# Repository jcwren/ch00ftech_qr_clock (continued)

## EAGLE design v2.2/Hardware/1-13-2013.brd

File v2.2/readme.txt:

_      ___   ___   __ _            _     
      | |    / _ \ / _ \ / _| |          | |    
   ___| |__ | | | | | | | |_| |_ ___  ___| |__  
  / __| '_ \| | | | | | |  _| __/ _ \/ __| '_ \ 
 | (__| | | | |_| | |_| | | | ||  __/ (__| | | |
  \___|_| |_|\___/ \___/|_|  \__\___|\___|_| |_|
                                                
QR Clock Readme v2.1 4/2/2012

By: Michael Ciuffo
ch00f@ch00ftech.com

http://ch00ftech.com/qrclock

*********************
*Package Description*
*********************

This package contains the following two folders:

--Hardware
Eagle files for schematic and PCB layout of the device along with a PNG schematic.  Digikey part numbers are included in part attributes. The symbol for D7 is backwards in the schematic.  Photodiodes should be reverse biased.

--Firmware
Firmware and Makefile for the QR clock.  Should compile with with avrdude version 5.11.1.

**********
*Versions*
**********

2.2 - Fixed a bug resulting from a misinterpretation of the QR code generation process.  After the XOR step, only the *first* zero is supposed to be removed even if more than one is there.  Modified code to only remove first zero.  This bug caused an invalid QR code with very specific inputs such as “00Y9PT0040016002”

**********
*Warnings*
**********

THIS IS NOT A TUTORIAL! These are the design files that I used to create what you see on my blog.  They are meant to be used as reference only.  If you do not understand how the project is supposed to work, do not begin working on it.  Given how haphazardly a lot of my projects are put together, in all likelihood, the designs presented herein won't actually work due to changes I made post publication.

I am a EE, not a coder.  My programming practices are questionable at best.  If you learn anything from working on this project, please don't let it be how to code like I do.

*********
*License*
*********

The contents of this package are released to you under the Creative Commons Attribution-NonCommercial 3.0 Unported license.

This means that you are free to distribute this package and edit it as you see fit.  All works based on this package must provide attribution in some form to me.  A simple link to the blog post along with a description of what you used will suffice.

You may not use this package for any commercial ventures without my consent (but I'm usually cool with it, you just have to send me an email and ask nicely).

More information here:

http://creativecommons.org/licenses/by-nc/3.0/deed.en_US

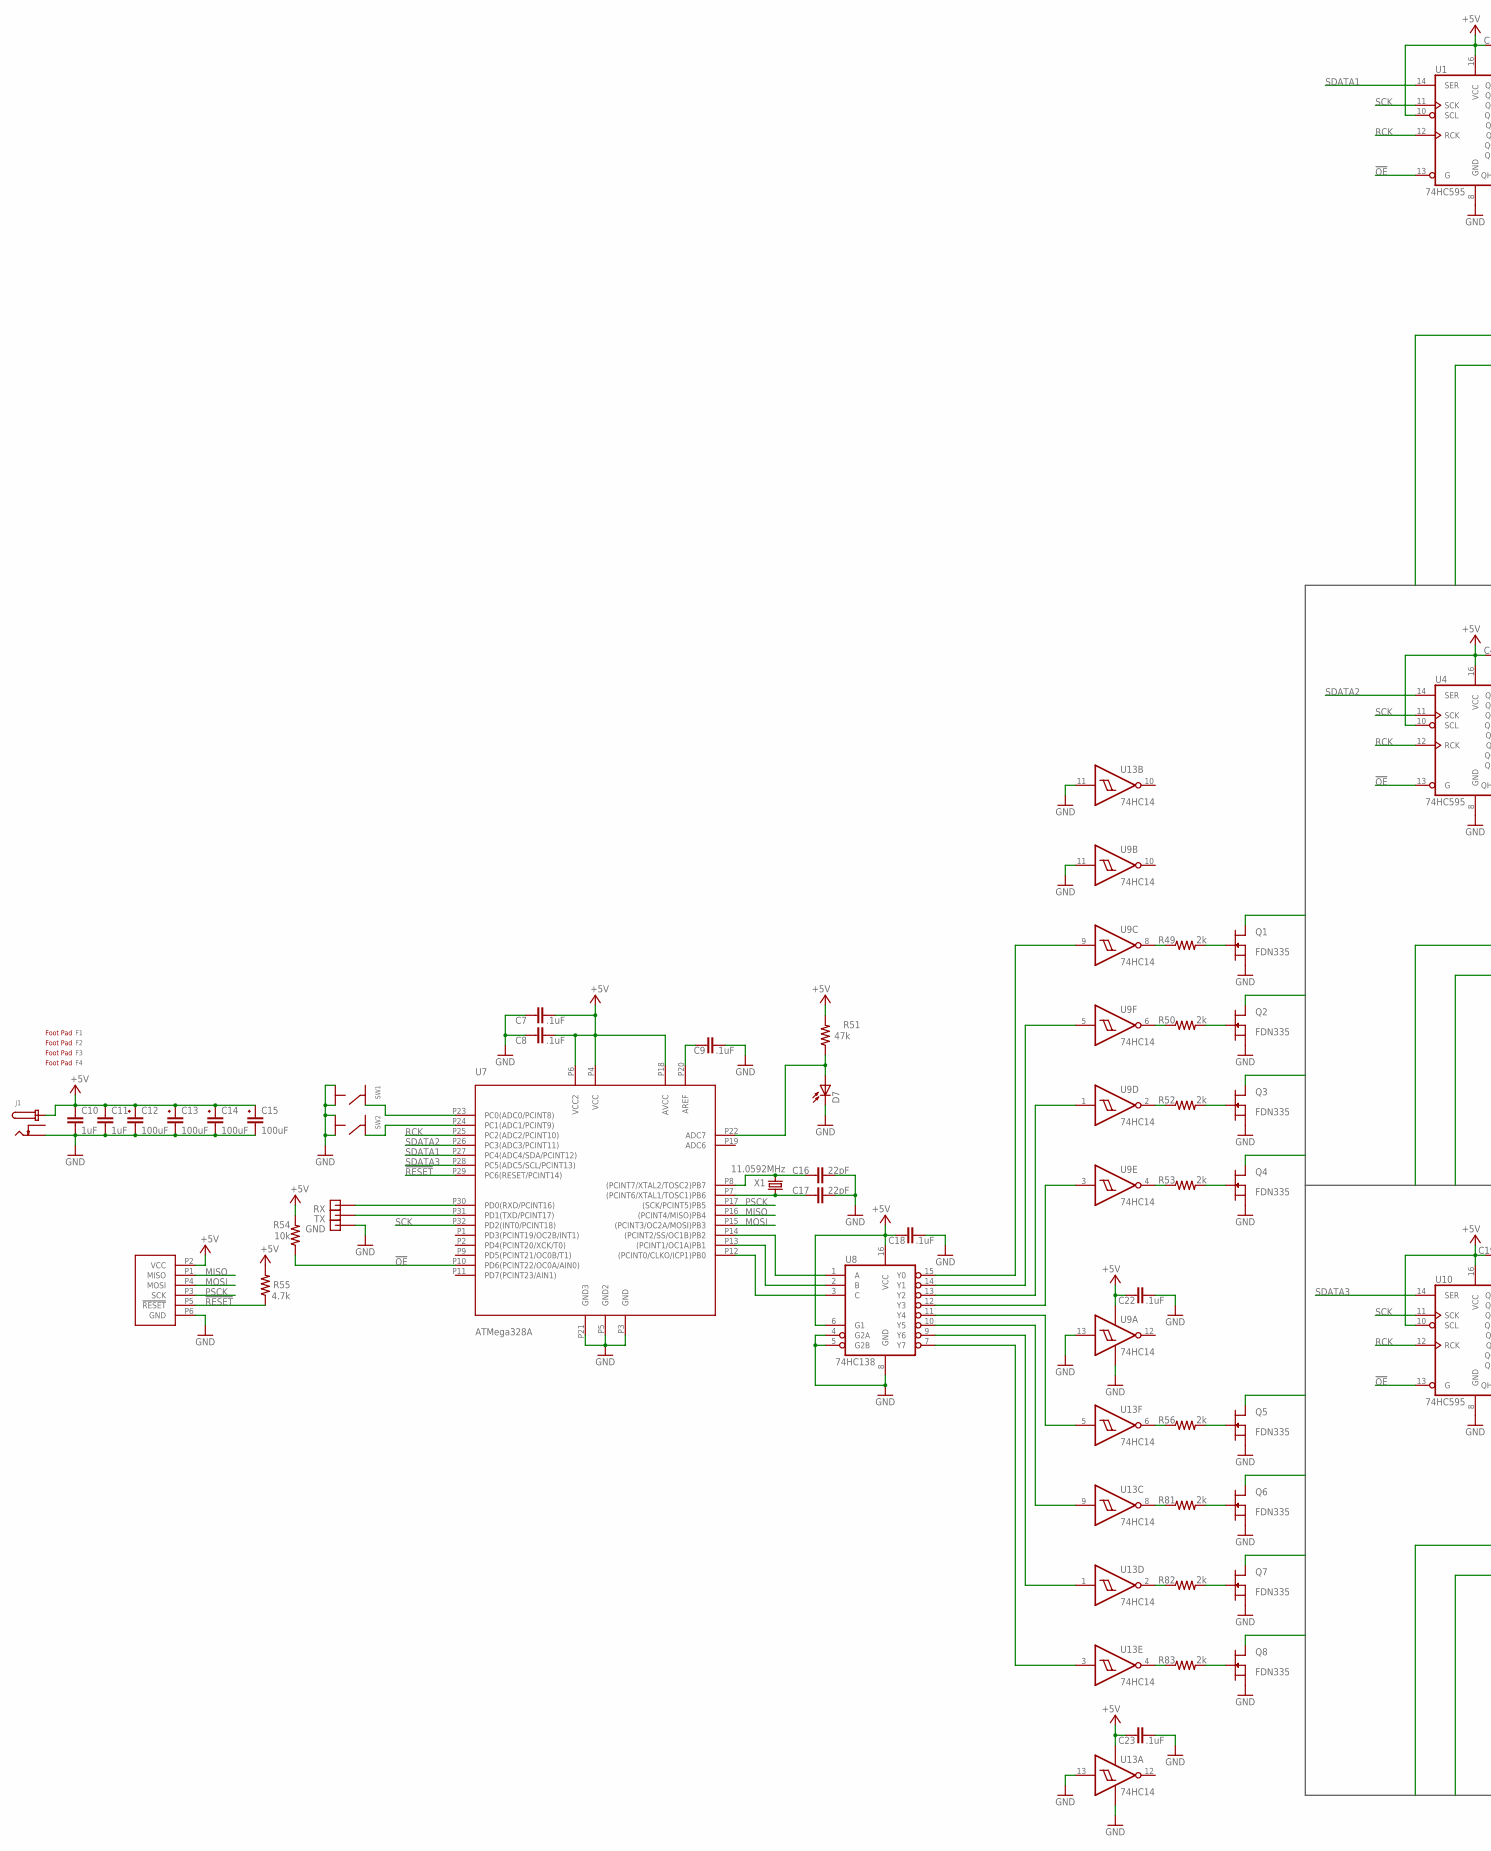
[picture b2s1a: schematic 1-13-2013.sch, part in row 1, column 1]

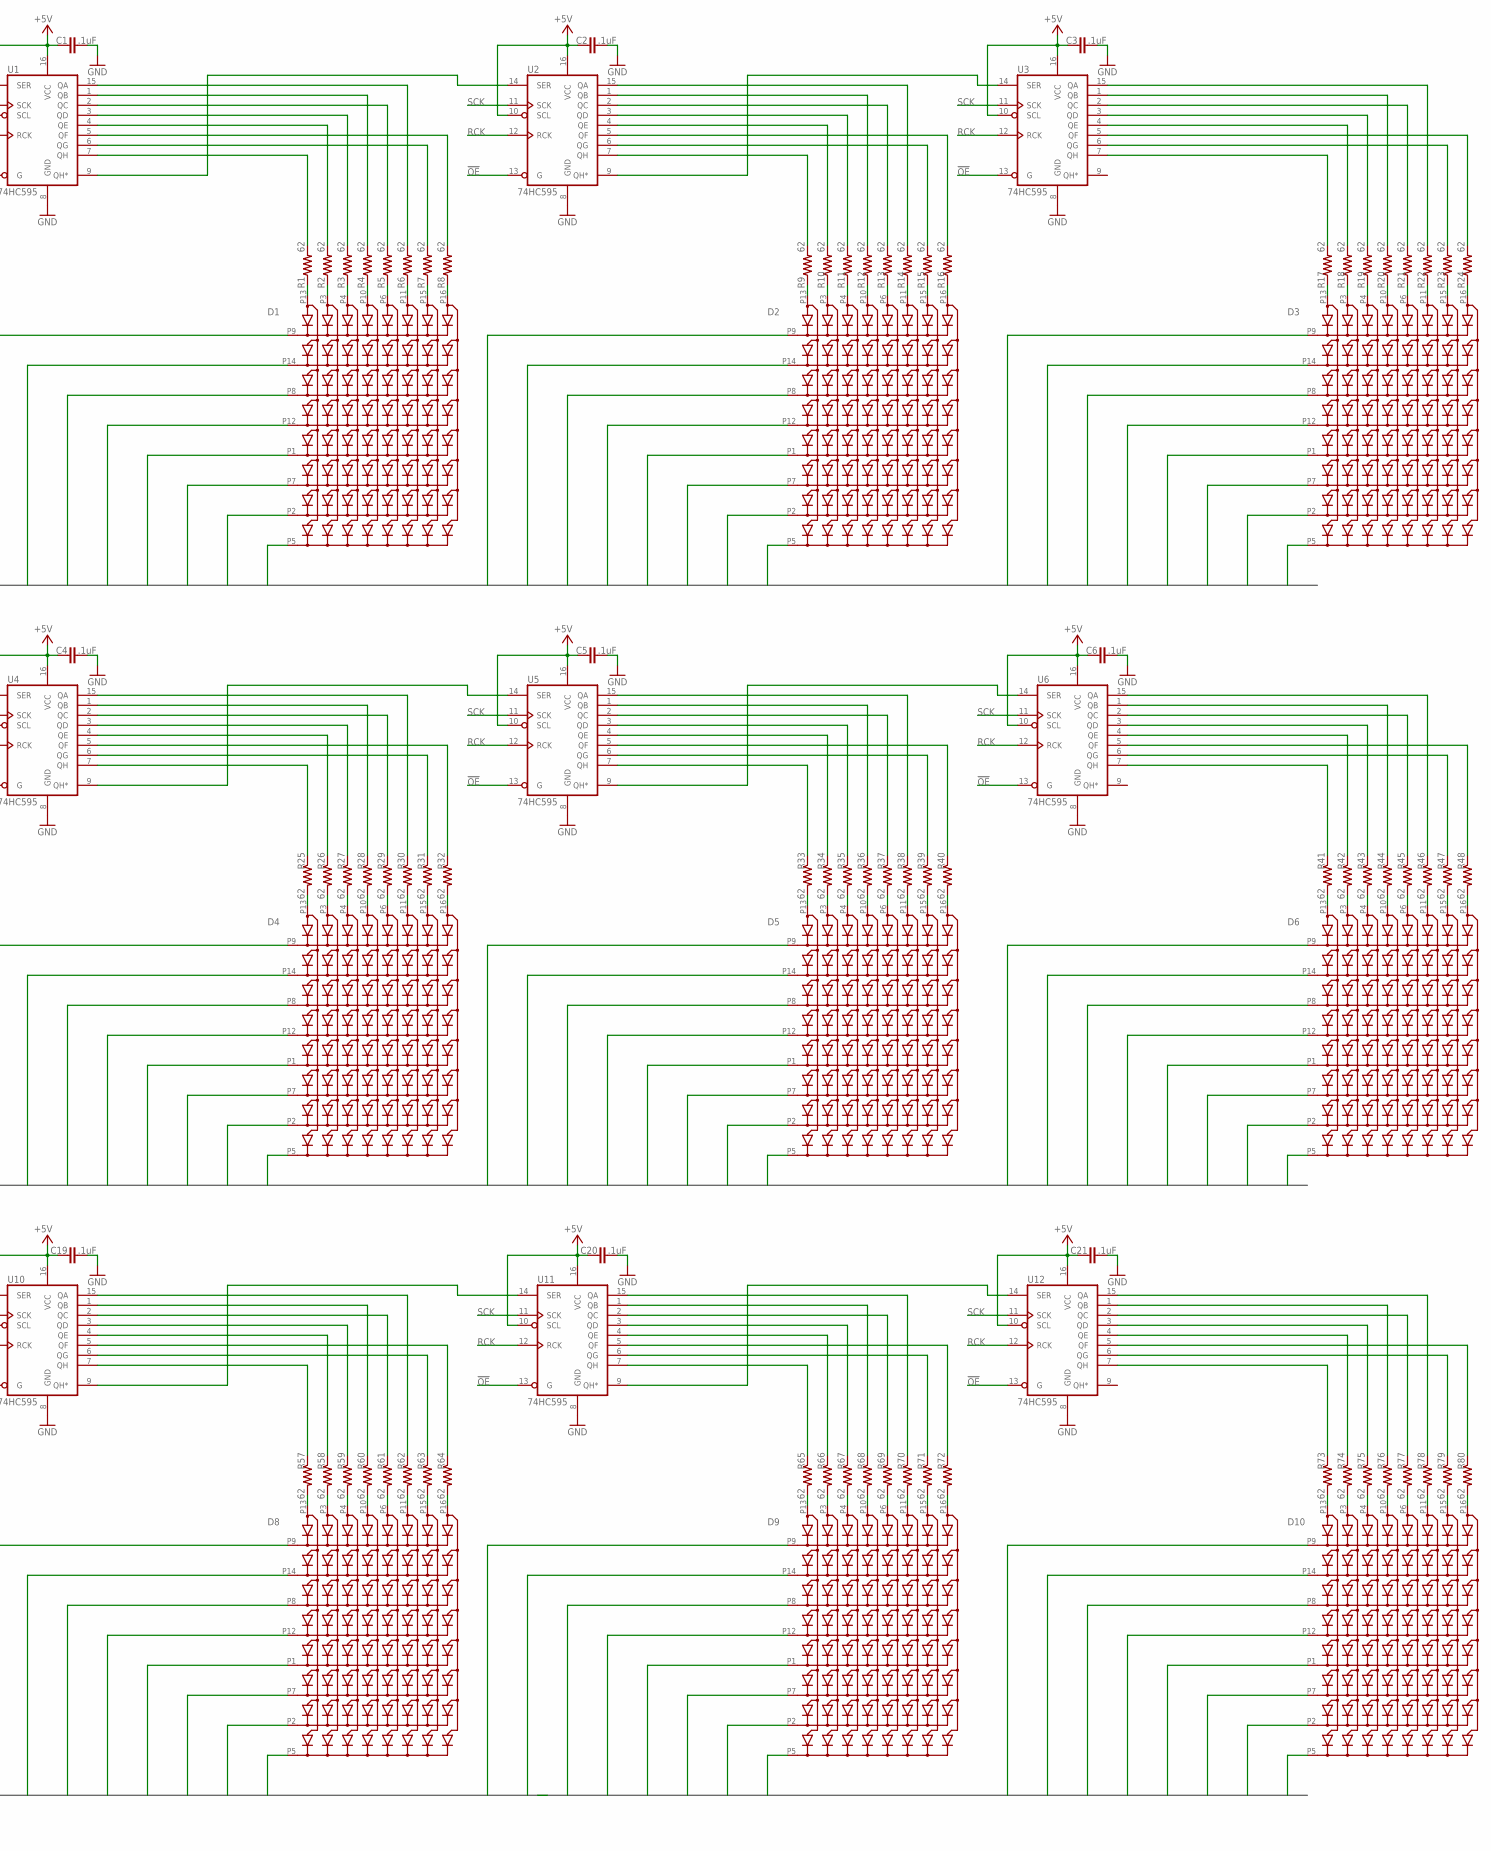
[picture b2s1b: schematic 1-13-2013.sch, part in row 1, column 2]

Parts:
C1, C2, C3, C4, C5, C6, C7, C8, C9, C18, C19, C20, C21, C22, C23: .1uF; 0603/1608METRIC
C10, C11: 1uF; 0603/1608METRIC
C12, C13: 100uF; CAP-UWX-6.3
C14, C15: 100uF; CAP-UWX-6.3; MANPARTNO UWX1C101MCL1GB
C16, C17: 22pF; 0603/1608METRIC; VOLTAGE 25V
D1, D2, D3, D4, D5, D6, D8, D9, D10: WHITE; HS-2085BX
D7: TEPT4400; LED3MM
F1, F2, F3, F4: RUBBER-FOOT; SJ-5518
GND: HEADERPIN
J1: DC-BARREL-JACK-SWITCH; PJ-075DH-SMT-TR
J2: PROGHEADER-PINS; ATMEL-PROGRAMMING-HEADER
Q1, Q2, Q3, Q4, Q5, Q6, Q7, Q8: FDN335; SOT23
R1: 62; 0603/1608METRIC
R2, R3, R4, R5, R6, R7, R8, R9, R10, R11, R12, R13, R14, R15, R16, R17, R18, R19, R20, R21, R22, R23, R24, R25, R26, R27, R28, R29, R30, R31, R32, R33, R34, R35, R36, R37, R38, R39, R40, R41, R42, R43, R44, R45, R46, R47, R48, R57, R58, R59, R60, R61, R62, R63, R64, R65, R66, R67, R68, R69, R70, R71, R72, R73, R74, R75, R76, R77, R78, R79, R80: 62; 0603/1608METRIC; TOLERANCE 5%; MANPARTNO RC0603JR-0762RL
R49, R50, R52, R53, R56, R81, R82, R83: 2k; 0603/1608METRIC
R51: 47k; 0603/1608METRIC
R54: 10k; 0603/1608METRIC
R55: 4.7k; 0603/1608METRIC
RX: HEADERPIN
SW1, SW2: 4mm; PTS645SM43SMTRLFS; MANPARTNO PTS645SM43SMTR LFS
TX: HEADERPIN
U1, U2, U3, U4, U5, U6, U10, U11, U12: 74HC595; SO16
U7: ATMega328A; TQFP-32
U8: 74HC138; SO16
U9, U13: 74HC14; SO14
X1: 11.0592MHz; HC49UP; MANPARTNO 9C-11.0592MEEJ-T

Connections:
!OE: R54.P1 (1), U1.13 (G), U2.13 (G), U3.13 (G), U4.13 (G), U5.13 (G), U6.13 (G), U7.P10 (PD6(PCINT22/OC0A/AIN0)), U10.13 (G), U11.13 (G), U12.13 (G)
!RESET: J2.P5 (!RESET), R55.P1 (1), U7.P29 (PC6(RESET/PCINT14))
+5V: C1.P1 (1), C2.P1 (1), C3.P1 (1), C4.P1 (1), C5.P1 (1), C6.P1 (1), C7.P1 (1), C8.P1 (1), C10.P1 (1), C11.P1 (1), C12.+ (1), C13.+ (1), C14.+ (1), C15.+ (1), C18.P1 (1), C19.P1 (1), C20.P1 (1), C21.P1 (1), C22.P1 (1), C23.P1 (1), J1.1 (PIN), J2.P2 (VCC), R51.P2 (2), R54.P2 (2), R55.P2 (2), U1.10 (SCL), U1.16 (VCC), U2.10 (SCL), U2.16 (VCC), U3.10 (SCL), U3.16 (VCC), U4.10 (SCL), U4.16 (VCC), U5.10 (SCL), U5.16 (VCC), U6.10 (SCL), U6.16 (VCC), U7.P4 (VCC), U7.P6 (VCC2), U7.P18 (AVCC), U8.6 (G1), U8.16 (VCC), U9.14 (VCC), U10.10 (SCL), U10.16 (VCC), U11.10 (SCL), U11.16 (VCC), U12.10 (SCL), U12.16 (VCC), U13.14 (VCC)
GND: C1.P2 (2), C2.P2 (2), C3.P2 (2), C4.P2 (2), C5.P2 (2), C6.P2 (2), C7.P2 (2), C8.P2 (2), C9.P2 (2), C10.P2 (2), C11.P2 (2), C12.- (2), C13.- (2), C14.- (2), C15.- (2), C16.P2 (2), C17.P2 (2), C18.P2 (2), C19.P2 (2), C20.P2 (2), C21.P2 (2), C22.P2 (2), C23.P2 (2), D7.K (C), GND.P$1, J1.2 (BARREL), J2.P6 (GND), Q1.2 (S), Q2.2 (S), Q3.2 (S), Q4.2 (S), Q5.2 (S), Q6.2 (S), Q7.2 (S), Q8.2 (S), SW1.P3, SW1.P4, SW2.P3, SW2.P4, U1.8 (GND), U2.8 (GND), U3.8 (GND), U4.8 (GND), U5.8 (GND), U6.8 (GND), U7.P3 (GND), U7.P5 (GND2), U7.P21 (GND3), U8.4 (G2A), U8.5 (G2B), U8.8 (GND), U9.7 (GND), U9.11 (I), U9.13 (I), U10.8 (GND), U11.8 (GND), U12.8 (GND), U13.7 (GND), U13.11 (I), U13.13 (I)
MISO: J2.P1 (MISO), U7.P16 ((PCINT4/MISO)PB4)
MOSI: J2.P4 (MOSI), U7.P15 ((PCINT3/OC2A/MOSI)PB3)
unnamed: D1.P13 (C1), R1.P1 (1)
unnamed: R4.P2 (2), U1.1 (QB)
unnamed: D1.P3 (C2), R2.P1 (1)
unnamed: R5.P2 (2), U1.2 (QC)
unnamed: D1.P4 (C3), R3.P1 (1)
unnamed: R14.P2 (2), U2.15 (QA)
unnamed: D1.P10 (C4), R4.P1 (1)
unnamed: R13.P2 (2), U2.2 (QC)
unnamed: D1.P6 (C5), R5.P1 (1)
unnamed: R12.P2 (2), U2.1 (QB)
unnamed: D1.P11 (C6), R6.P1 (1)
unnamed: R11.P2 (2), U2.3 (QD)
unnamed: D1.P15 (C7), R7.P1 (1)
unnamed: R10.P2 (2), U2.4 (QE)
unnamed: D1.P16 (C8), R8.P1 (1)
unnamed: R16.P2 (2), U2.5 (QF)
unnamed: U8.15 (Y0), U9.9 (I)
unnamed: D2.P13 (C1), R9.P1 (1)
unnamed: R21.P2 (2), U3.2 (QC)
unnamed: D2.P3 (C2), R10.P1 (1)
unnamed: R20.P2 (2), U3.1 (QB)
unnamed: D2.P4 (C3), R11.P1 (1)
unnamed: R19.P2 (2), U3.3 (QD)
unnamed: D2.P10 (C4), R12.P1 (1)
unnamed: R18.P2 (2), U3.4 (QE)
unnamed: D2.P6 (C5), R13.P1 (1)
unnamed: R24.P2 (2), U3.5 (QF)
unnamed: D2.P11 (C6), R14.P1 (1)
unnamed: R32.P1 (1), U4.5 (QF)
unnamed: D2.P15 (C7), R15.P1 (1)
unnamed: R25.P1 (1), U4.7 (QH)
unnamed: D2.P16 (C8), R16.P1 (1)
unnamed: R52.P1 (1), U9.2 (O)
unnamed: R50.P1 (1), U9.6 (O)
unnamed: R49.P1 (1), U9.8 (O)
unnamed: R53.P1 (1), U9.4 (O)
unnamed: R83.P1 (1), U13.4 (O)
unnamed: R82.P1 (1), U13.2 (O)
unnamed: R81.P1 (1), U13.8 (O)
unnamed: R56.P1 (1), U13.6 (O)
unnamed: C17.P1 (1), U7.P7 ((PCINT6/XTAL1/TOSC1)PB6), X1.1
unnamed: R7.P2 (2), U1.6 (QG)
unnamed: TX.P$1, U7.P31 (PD1(TXD/PCINT17))
unnamed: C16.P1 (1), U7.P8 ((PCINT7/XTAL2/TOSC2)PB7), X1.2
unnamed: RX.P$1, U7.P30 (PD0(RXD/PCINT16))
unnamed: Q3.1 (G), R52.P2 (2)
unnamed: SW2.P2, U7.P24 (PC1(ADC1/PCINT9))
unnamed: SW1.P2, U7.P23 (PC0(ADC0/PCINT8))
unnamed: R1.P2 (2), U1.7 (QH)
unnamed: Q1.1 (G), R49.P2 (2)
unnamed: R8.P2 (2), U1.5 (QF)
unnamed: R2.P2 (2), U1.4 (QE)
unnamed: R3.P2 (2), U1.3 (QD)
unnamed: R31.P1 (1), U4.6 (QG)
unnamed: R26.P1 (1), U4.4 (QE)
unnamed: R6.P2 (2), U1.15 (QA)
unnamed: R27.P1 (1), U4.3 (QD)
unnamed: R29.P1 (1), U4.2 (QC)
unnamed: R30.P1 (1), U4.15 (QA)
unnamed: R33.P1 (1), U5.7 (QH)
unnamed: R39.P1 (1), U5.6 (QG)
unnamed: R40.P1 (1), U5.5 (QF)
unnamed: R34.P1 (1), U5.4 (QE)
unnamed: R35.P1 (1), U5.3 (QD)
unnamed: R36.P1 (1), U5.1 (QB)
unnamed: R37.P1 (1), U5.2 (QC)
unnamed: R38.P1 (1), U5.15 (QA)
unnamed: R41.P1 (1), U6.7 (QH)
unnamed: R47.P1 (1), U6.6 (QG)
unnamed: R46.P1 (1), U6.15 (QA)
unnamed: R45.P1 (1), U6.2 (QC)
unnamed: R44.P1 (1), U6.1 (QB)
unnamed: R43.P1 (1), U6.3 (QD)
unnamed: U8.14 (Y1), U9.5 (I)
unnamed: U4.9 (QH*), U5.14 (SER)
unnamed: U5.9 (QH*), U6.14 (SER)
unnamed: U8.13 (Y2), U9.1 (I)
unnamed: U1.9 (QH*), U2.14 (SER)
unnamed: U2.9 (QH*), U3.14 (SER)
unnamed: R42.P1 (1), U6.4 (QE)
unnamed: R48.P1 (1), U6.5 (QF)
unnamed: R57.P1 (1), U10.7 (QH)
unnamed: R63.P1 (1), U10.6 (QG)
unnamed: R64.P1 (1), U10.5 (QF)
unnamed: R58.P1 (1), U10.4 (QE)
unnamed: R59.P1 (1), U10.3 (QD)
unnamed: R15.P2 (2), U2.6 (QG)
unnamed: R61.P1 (1), U10.2 (QC)
unnamed: R60.P1 (1), U10.1 (QB)
unnamed: R62.P1 (1), U10.15 (QA)
unnamed: R65.P1 (1), U11.7 (QH)
unnamed: R71.P1 (1), U11.6 (QG)
unnamed: R72.P1 (1), U11.5 (QF)
unnamed: R66.P1 (1), U11.4 (QE)
unnamed: R67.P1 (1), U11.3 (QD)
unnamed: R69.P1 (1), U11.2 (QC)
unnamed: R9.P2 (2), U2.7 (QH)
unnamed: R68.P1 (1), U11.1 (QB)
unnamed: R70.P1 (1), U11.15 (QA)
unnamed: R73.P1 (1), U12.7 (QH)
unnamed: R79.P1 (1), U12.6 (QG)
unnamed: R80.P1 (1), U12.5 (QF)
unnamed: R74.P1 (1), U12.4 (QE)
unnamed: R75.P1 (1), U12.3 (QD)
unnamed: R77.P1 (1), U12.2 (QC)
unnamed: R76.P1 (1), U12.1 (QB)
unnamed: R78.P1 (1), U12.15 (QA)
unnamed: U10.9 (QH*), U11.14 (SER)
unnamed: U11.9 (QH*), U12.14 (SER)
unnamed: U8.12 (Y3), U9.3 (I)
unnamed: U8.11 (Y4), U13.5 (I)
unnamed: U8.10 (Y5), U13.9 (I)
unnamed: U8.9 (Y6), U13.1 (I)
unnamed: U8.7 (Y7), U13.3 (I)
unnamed: D7.A, R51.P1 (1), U7.P22 (ADC7)
unnamed: D3.P13 (C1), R17.P1 (1)
unnamed: D3.P3 (C2), R18.P1 (1)
unnamed: D3.P4 (C3), R19.P1 (1)
unnamed: D3.P10 (C4), R20.P1 (1)
unnamed: D3.P6 (C5), R21.P1 (1)
unnamed: D3.P11 (C6), R22.P1 (1)
unnamed: D3.P15 (C7), R23.P1 (1)
unnamed: D3.P16 (C8), R24.P1 (1)
unnamed: R17.P2 (2), U3.7 (QH)
unnamed: R23.P2 (2), U3.6 (QG)
unnamed: R22.P2 (2), U3.15 (QA)
unnamed: U7.P12 ((PCINT0/CLKO/ICP1)PB0), U8.3 (C)
unnamed: U7.P13 ((PCINT1/OC1A)PB1), U8.2 (B)
unnamed: U7.P14 ((PCINT2/SS/OC1B)PB2), U8.1 (A)
unnamed: C9.P1 (1), U7.P20 (AREF)
unnamed: D4.P13 (C1), R25.P2 (2)
unnamed: D4.P3 (C2), R26.P2 (2)
unnamed: D4.P4 (C3), R27.P2 (2)
unnamed: D4.P10 (C4), R28.P2 (2)
unnamed: D4.P6 (C5), R29.P2 (2)
unnamed: D4.P11 (C6), R30.P2 (2)
unnamed: D4.P15 (C7), R31.P2 (2)
unnamed: D4.P16 (C8), R32.P2 (2)
unnamed: R28.P1 (1), U4.1 (QB)
unnamed: Q7.1 (G), R82.P2 (2)
unnamed: Q2.1 (G), R50.P2 (2)
unnamed: Q4.1 (G), R53.P2 (2)
unnamed: Q5.1 (G), R56.P2 (2)
unnamed: Q6.1 (G), R81.P2 (2)
unnamed: Q8.1 (G), R83.P2 (2)
unnamed: D5.P13 (C1), R33.P2 (2)
unnamed: D5.P3 (C2), R34.P2 (2)
unnamed: D5.P4 (C3), R35.P2 (2)
unnamed: D5.P10 (C4), R36.P2 (2)
unnamed: D5.P6 (C5), R37.P2 (2)
unnamed: D5.P11 (C6), R38.P2 (2)
unnamed: D5.P15 (C7), R39.P2 (2)
unnamed: D5.P16 (C8), R40.P2 (2)
unnamed: D6.P13 (C1), R41.P2 (2)
unnamed: D6.P3 (C2), R42.P2 (2)
unnamed: D6.P4 (C3), R43.P2 (2)
unnamed: D6.P10 (C4), R44.P2 (2)
unnamed: D6.P6 (C5), R45.P2 (2)
unnamed: D6.P11 (C6), R46.P2 (2)
unnamed: D6.P15 (C7), R47.P2 (2)
unnamed: D6.P16 (C8), R48.P2 (2)
unnamed: D8.P13 (C1), R57.P2 (2)
unnamed: D8.P3 (C2), R58.P2 (2)
unnamed: D8.P4 (C3), R59.P2 (2)
unnamed: D8.P10 (C4), R60.P2 (2)
unnamed: D8.P6 (C5), R61.P2 (2)
unnamed: D8.P11 (C6), R62.P2 (2)
unnamed: D8.P15 (C7), R63.P2 (2)
unnamed: D8.P16 (C8), R64.P2 (2)
unnamed: D9.P13 (C1), R65.P2 (2)
unnamed: D9.P3 (C2), R66.P2 (2)
unnamed: D9.P4 (C3), R67.P2 (2)
unnamed: D9.P10 (C4), R68.P2 (2)
unnamed: D9.P6 (C5), R69.P2 (2)
unnamed: D9.P11 (C6), R70.P2 (2)
unnamed: D9.P15 (C7), R71.P2 (2)
unnamed: D9.P16 (C8), R72.P2 (2)
unnamed: D10.P13 (C1), R73.P2 (2)
unnamed: D10.P3 (C2), R74.P2 (2)
unnamed: D10.P4 (C3), R75.P2 (2)
unnamed: D10.P10 (C4), R76.P2 (2)
unnamed: D10.P6 (C5), R77.P2 (2)
unnamed: D10.P11 (C6), R78.P2 (2)
unnamed: D10.P15 (C7), R79.P2 (2)
unnamed: D10.P16 (C8), R80.P2 (2)
PSCK: J2.P3 (SCK), U7.P17 ((SCK/PCINT5)PB5)
RCK: U1.12 (RCK), U2.12 (RCK), U3.12 (RCK), U4.12 (RCK), U5.12 (RCK), U6.12 (RCK), U7.P25 (PC2(ADC2/PCINT10)), U10.12 (RCK), U11.12 (RCK), U12.12 (RCK)
ROW0: D1.P9 (R1), D2.P9 (R1), D3.P9 (R1), D4.P9 (R1), D5.P9 (R1), D6.P9 (R1), D8.P9 (R1), D9.P9 (R1), D10.P9 (R1), Q1.3 (D)
ROW1: D1.P14 (R2), D2.P14 (R2), D3.P14 (R2), D4.P14 (R2), D5.P14 (R2), D6.P14 (R2), D8.P14 (R2), D9.P14 (R2), D10.P14 (R2), Q2.3 (D)
ROW2: D1.P8 (R3), D2.P8 (R3), D3.P8 (R3), D4.P8 (R3), D5.P8 (R3), D6.P8 (R3), D8.P8 (R3), D9.P8 (R3), D10.P8 (R3), Q3.3 (D)
ROW3: D1.P12 (R4), D2.P12 (R4), D3.P12 (R4), D4.P12 (R4), D5.P12 (R4), D6.P12 (R4), D8.P12 (R4), D9.P12 (R4), D10.P12 (R4), Q4.3 (D)
ROW4: D1.P1 (R5), D2.P1 (R5), D3.P1 (R5), D4.P1 (R5), D5.P1 (R5), D6.P1 (R5), D8.P1 (R5), D9.P1 (R5), D10.P1 (R5), Q5.3 (D)
ROW5: D1.P7 (R6), D2.P7 (R6), D3.P7 (R6), D4.P7 (R6), D5.P7 (R6), D6.P7 (R6), D8.P7 (R6), D9.P7 (R6), D10.P7 (R6), Q6.3 (D)
ROW6: D1.P2 (R7), D2.P2 (R7), D3.P2 (R7), D4.P2 (R7), D5.P2 (R7), D6.P2 (R7), D8.P2 (R7), D9.P2 (R7), D10.P2 (R7), Q7.3 (D)
ROW7: D1.P5 (R8), D2.P5 (R8), D3.P5 (R8), D4.P5 (R8), D5.P5 (R8), D6.P5 (R8), D8.P5 (R8), D9.P5 (R8), D10.P5 (R8), Q8.3 (D)
SCK: U1.11 (SCK), U2.11 (SCK), U3.11 (SCK), U4.11 (SCK), U5.11 (SCK), U6.11 (SCK), U7.P32 (PD2(INT0/PCINT18)), U10.11 (SCK), U11.11 (SCK), U12.11 (SCK)
SDATA1: U1.14 (SER), U7.P27 (PC4(ADC4/SDA/PCINT12))
SDATA2: U4.14 (SER), U7.P26 (PC3(ADC3/PCINT11))
SDATA3: U7.P28 (PC5(ADC5/SCL/PCINT13)), U10.14 (SER)

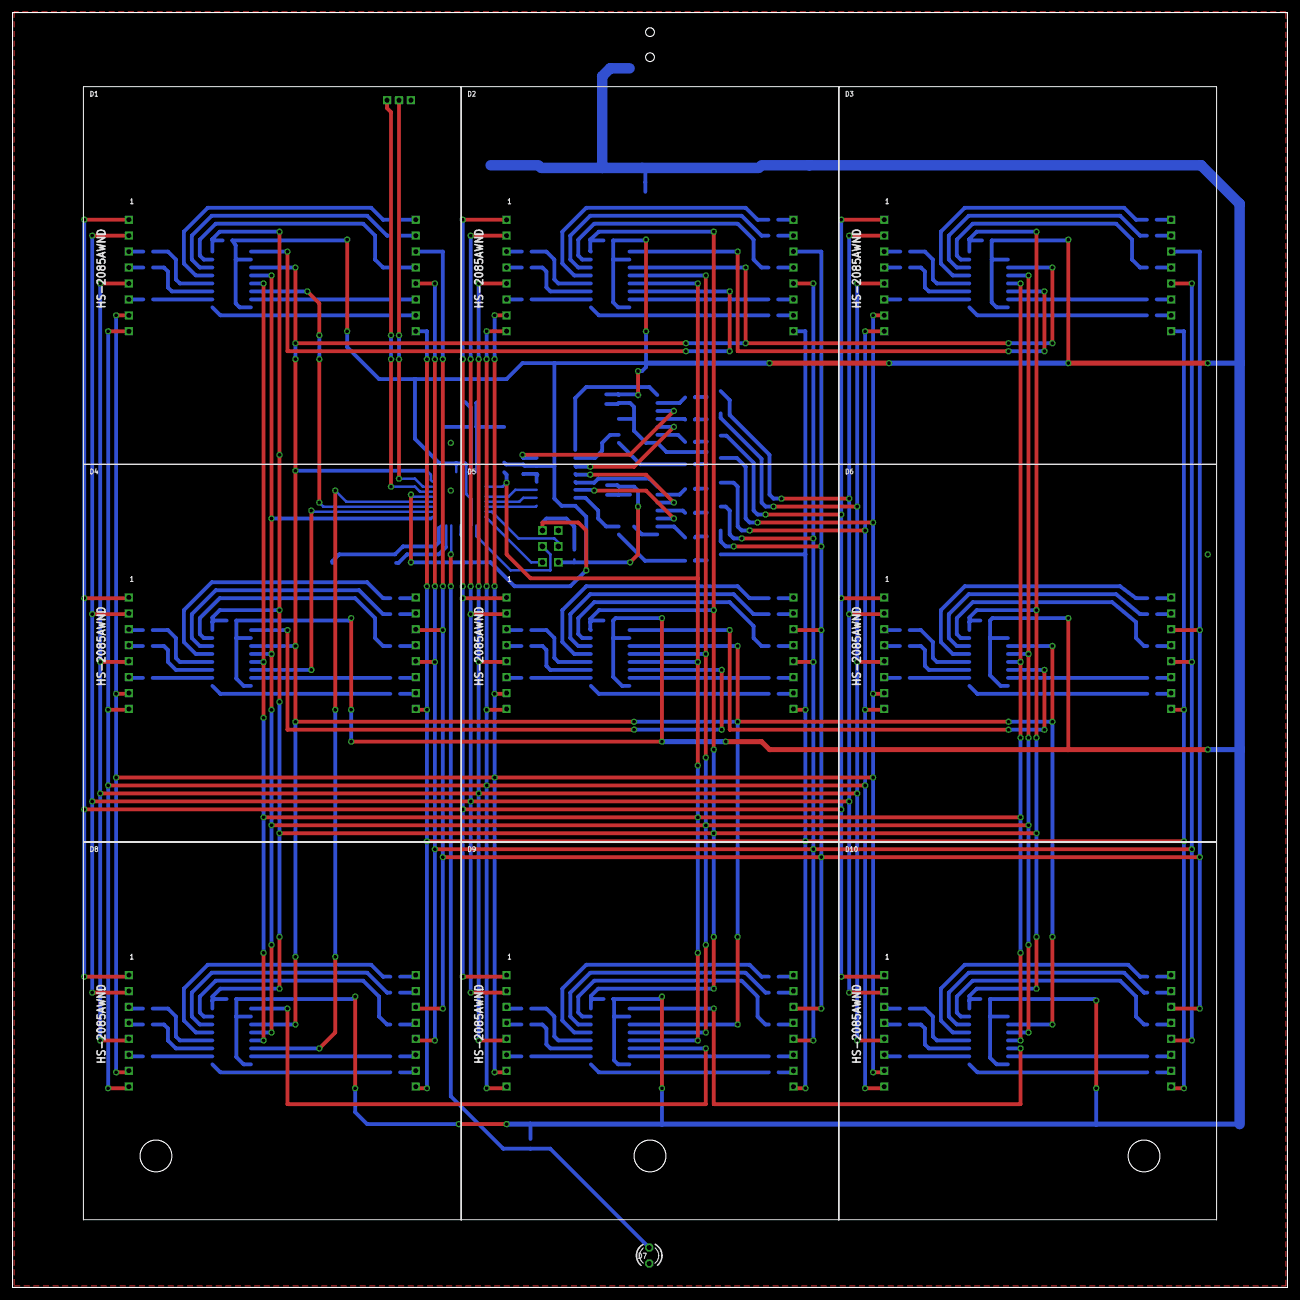
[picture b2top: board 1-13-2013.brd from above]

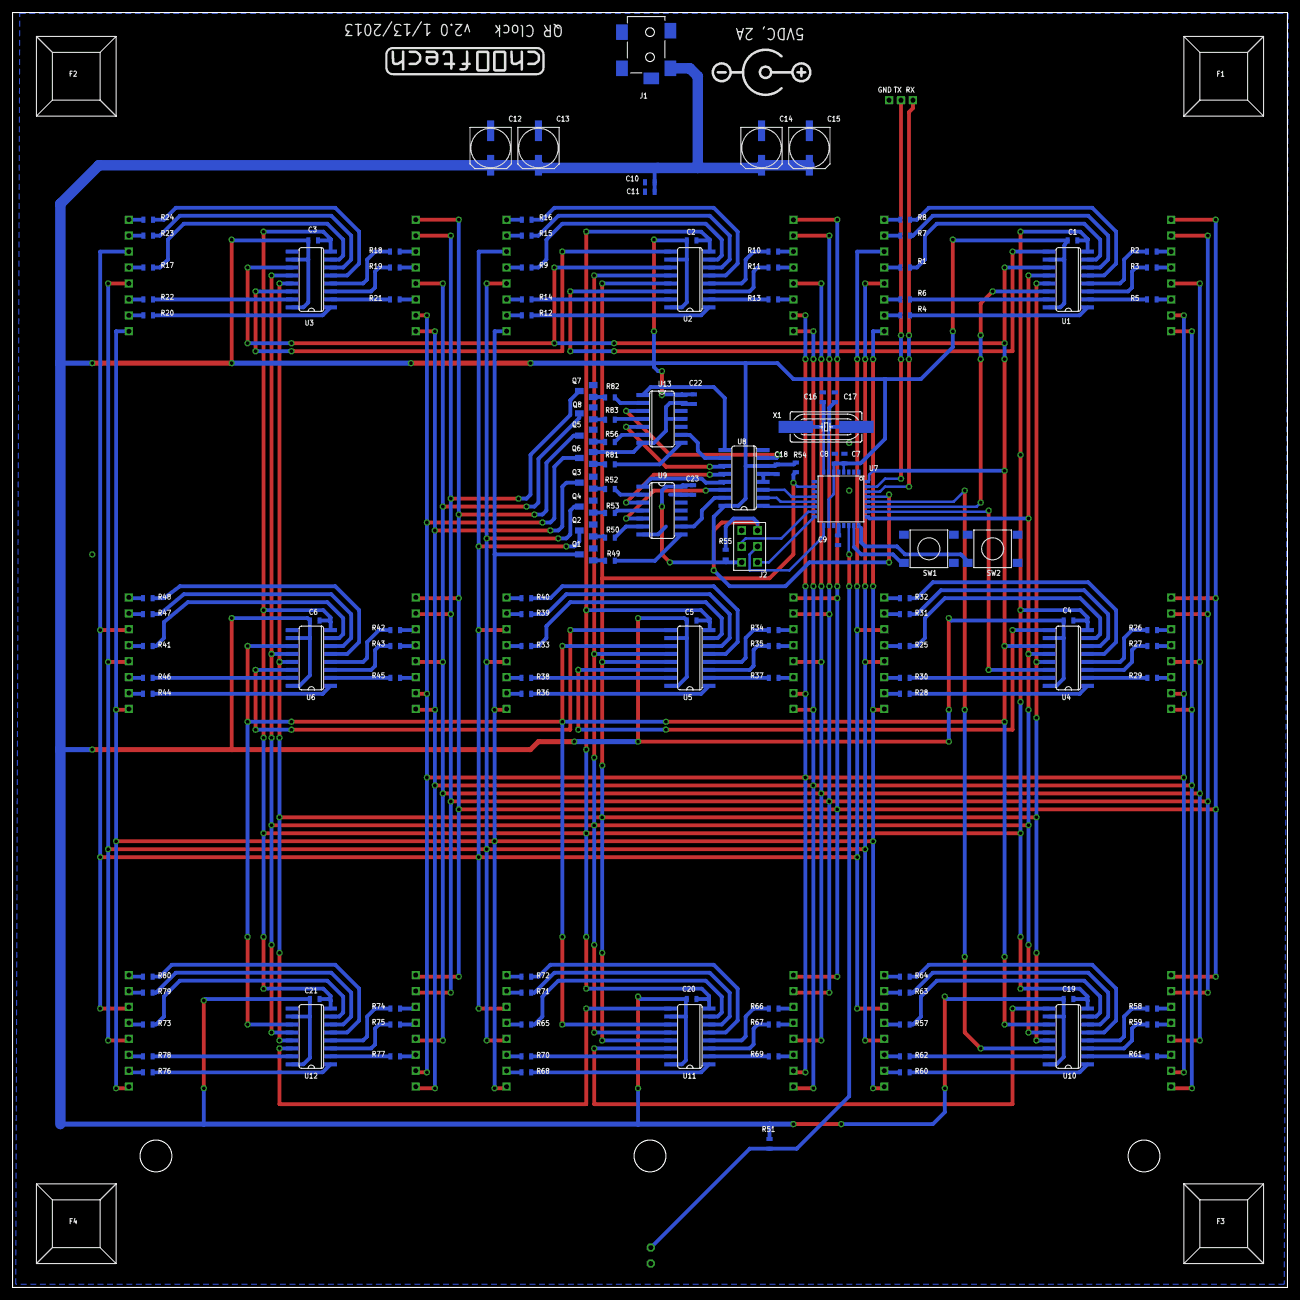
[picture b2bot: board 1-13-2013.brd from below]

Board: 2 copper layers, 203.2 x 203.2 mm, 149 parts (139 on the bottom side), 205 nets.

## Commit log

2020-12-30 Fixed formatting
2020-12-30 Removed .DS_Store files
2020-12-30 Updated comments
